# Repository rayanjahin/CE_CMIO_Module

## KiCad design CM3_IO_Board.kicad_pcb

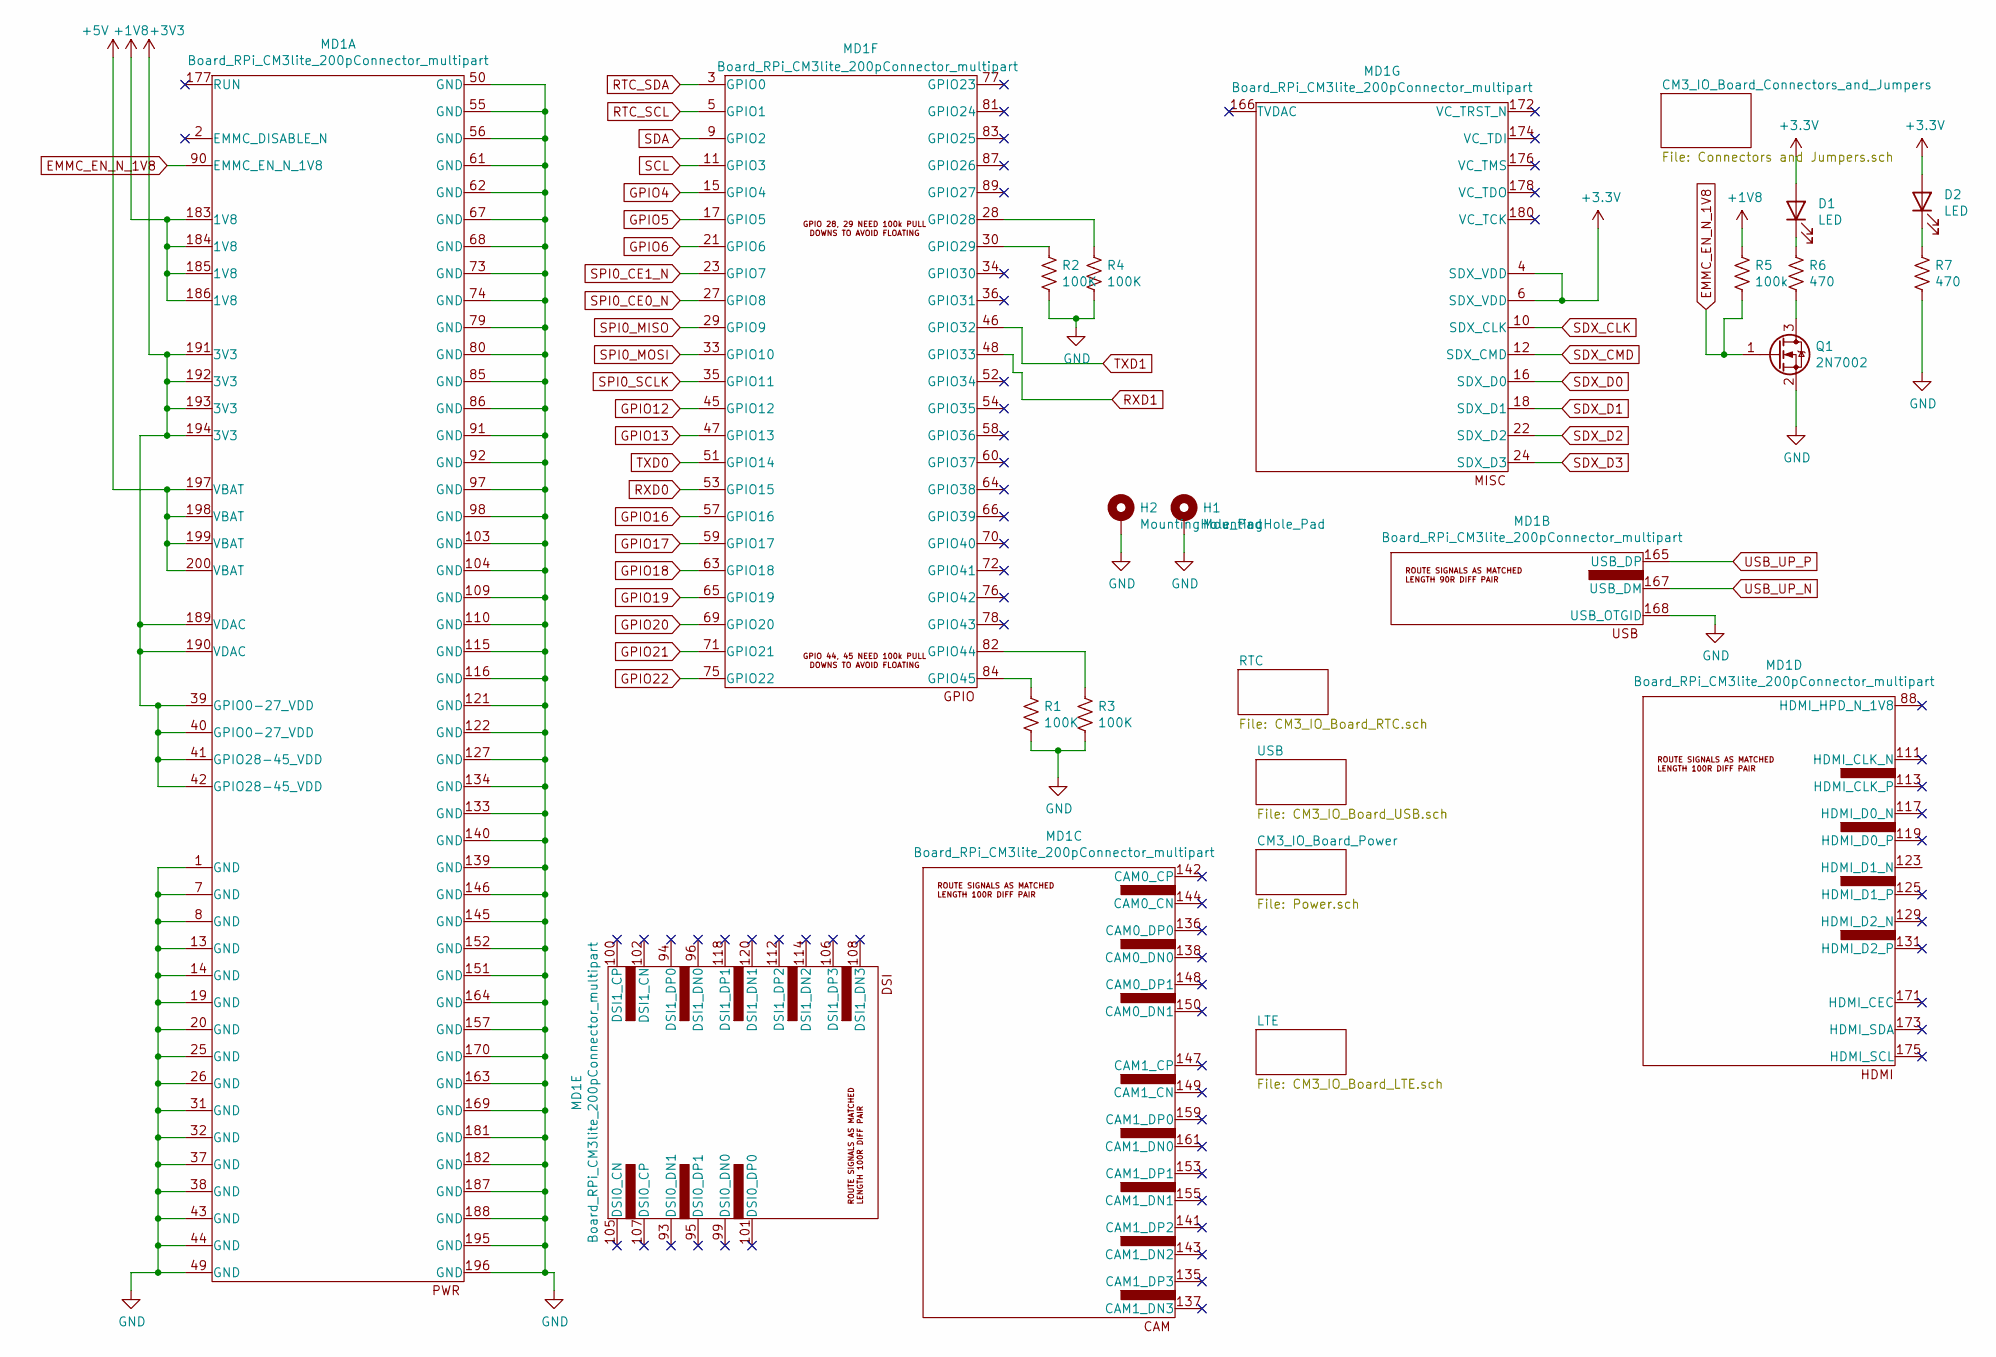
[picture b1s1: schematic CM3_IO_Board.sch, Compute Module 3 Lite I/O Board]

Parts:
D1, D2: LED; LED_1206_3216Metric
H1, H2: MountingHole_Pad; MountingHole_2.5mm_Pad_TopBottom
MD1: Board_RPi_CM3lite_200pConnector_multipart; Conn_TE-DDR2-SODIMM-0.6-200P-doublesided
Q1: 2N7002; SOT-23
R1, R2, R3, R4: 100K; R_1206_3216Metric
R5: 100k; R_1206_3216Metric
R6, R7: 470; R_1206_3216Metric

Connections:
+1V8: MD1.183 (1V8), MD1.184 (1V8), MD1.185 (1V8), MD1.186 (1V8), R5.1; also elsewhere on the board
+5V: MD1.197 (VBAT), MD1.198 (VBAT), MD1.199 (VBAT), MD1.200 (VBAT); also elsewhere on the board
EMMC_EN_N_1V8: MD1.90 (EMMC_EN_N_1V8), Q1.1 (G), R5.2
GND: H1.1, H2.1, MD1.1 (GND), MD1.7 (GND), MD1.8 (GND), MD1.13 (GND), MD1.14 (GND), MD1.19 (GND), MD1.20 (GND), MD1.25 (GND), MD1.26 (GND), MD1.31 (GND), MD1.32 (GND), MD1.37 (GND), MD1.38 (GND), MD1.43 (GND), MD1.44 (GND), MD1.49 (GND), MD1.50 (GND), MD1.55 (GND), MD1.56 (GND), MD1.61 (GND), MD1.62 (GND), MD1.67 (GND), MD1.68 (GND), MD1.73 (GND), MD1.74 (GND), MD1.79 (GND), MD1.80 (GND), MD1.85 (GND), MD1.86 (GND), MD1.91 (GND), MD1.92 (GND), MD1.97 (GND), MD1.98 (GND), MD1.103 (GND), MD1.104 (GND), MD1.109 (GND), MD1.110 (GND), MD1.115 (GND), MD1.116 (GND), MD1.121 (GND), MD1.122 (GND), MD1.127 (GND), MD1.133 (GND), MD1.134 (GND), MD1.139 (GND), MD1.140 (GND), MD1.145 (GND), MD1.146 (GND), MD1.151 (GND), MD1.152 (GND), MD1.157 (GND), MD1.163 (GND), MD1.164 (GND), MD1.168 (USB_OTGID), MD1.169 (GND), MD1.170 (GND), MD1.181 (GND), MD1.182 (GND), MD1.187 (GND), MD1.188 (GND), MD1.195 (GND), MD1.196 (GND), Q1.2 (S), R1.2, R2.2, R3.2, R4.2, R7.2; also elsewhere on the board
GPIO4: MD1.15 (GPIO4); also elsewhere on the board
GPIO5: MD1.17 (GPIO5); also elsewhere on the board
GPIO6: MD1.21 (GPIO6); also elsewhere on the board
GPIO12: MD1.45 (GPIO12); also elsewhere on the board
GPIO13: MD1.47 (GPIO13); also elsewhere on the board
GPIO16: MD1.57 (GPIO16); also elsewhere on the board
GPIO17: MD1.59 (GPIO17); also elsewhere on the board
GPIO18: MD1.63 (GPIO18); also elsewhere on the board
GPIO19: MD1.65 (GPIO19); also elsewhere on the board
GPIO20: MD1.69 (GPIO20); also elsewhere on the board
GPIO21: MD1.71 (GPIO21); also elsewhere on the board
GPIO22: MD1.75 (GPIO22); also elsewhere on the board
unnamed: D1.1 (K), R6.1
unnamed: D2.1 (K), R7.1
unnamed: MD1.28 (GPIO28), R4.1
unnamed: MD1.30 (GPIO29), R2.1
unnamed: MD1.82 (GPIO44), R3.1
unnamed: MD1.84 (GPIO45), R1.1
unnamed: Q1.3 (D), R6.2
RTC_SCL: MD1.5 (GPIO1); also elsewhere on the board
RTC_SDA: MD1.3 (GPIO0); also elsewhere on the board
RXD0: MD1.53 (GPIO15); also elsewhere on the board
RXD1: MD1.48 (GPIO33); also elsewhere on the board
SCL: MD1.11 (GPIO3); also elsewhere on the board
SDA: MD1.9 (GPIO2); also elsewhere on the board
SDX_CLK: MD1.10 (SDX_CLK); also elsewhere on the board
SDX_CMD: MD1.12 (SDX_CMD); also elsewhere on the board
SDX_D0: MD1.16 (SDX_D0); also elsewhere on the board
SDX_D1: MD1.18 (SDX_D1); also elsewhere on the board
SDX_D2: MD1.22 (SDX_D2); also elsewhere on the board
SDX_D3: MD1.24 (SDX_D3); also elsewhere on the board
SPI0_CE0_N: MD1.27 (GPIO8); also elsewhere on the board
SPI0_CE1_N: MD1.23 (GPIO7); also elsewhere on the board
SPI0_MISO: MD1.29 (GPIO9); also elsewhere on the board
SPI0_MOSI: MD1.33 (GPIO10); also elsewhere on the board
SPI0_SCLK: MD1.35 (GPIO11); also elsewhere on the board
TXD0: MD1.51 (GPIO14); also elsewhere on the board
TXD1: MD1.46 (GPIO32); also elsewhere on the board
USB_UP_N: MD1.167 (USB_DM); also elsewhere on the board
USB_UP_P: MD1.165 (USB_DP); also elsewhere on the board

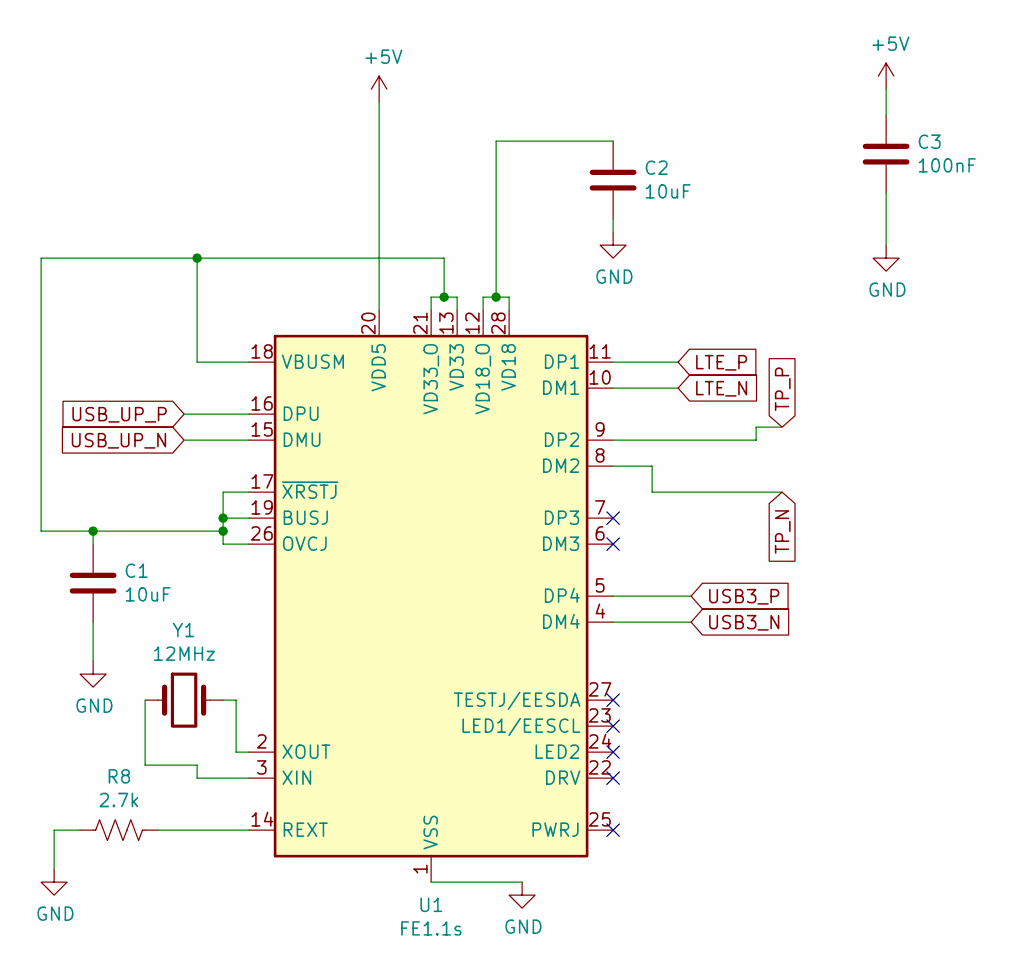
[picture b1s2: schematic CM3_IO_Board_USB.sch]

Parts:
C1, C2: 10uF; C_1206_3216Metric
C3: 100nF; C_0805_2012Metric
R8: 2.7k; R_1206_3216Metric
U1: FE1.1s; SSOP-28_3.9x9.9mm_P0.635mm
Y1: 12MHz; Crystal_HC18-U_Vertical

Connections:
+5V: C3.1, U1.20 (VDD5); also elsewhere on the board
GND: C1.2, C2.2, C3.2, R8.2, U1.1 (VSS); also elsewhere on the board
LTE_N: U1.10 (DM1); also elsewhere on the board
LTE_P: U1.11 (DP1); also elsewhere on the board
unnamed: C1.1, U1.13 (VD33), U1.17 (~XRSTJ), U1.18 (VBUSM), U1.19 (BUSJ), U1.21 (VD33_O), U1.26 (OVCJ)
unnamed: C2.1, U1.12 (VD18_O), U1.28 (VD18)
unnamed: R8.1, U1.14 (REXT)
unnamed: U1.2 (XOUT), Y1.2
unnamed: U1.3 (XIN), Y1.1
TP_N: U1.8 (DM2); also elsewhere on the board
TP_P: U1.9 (DP2); also elsewhere on the board
USB3_N: U1.4 (DM4); also elsewhere on the board
USB3_P: U1.5 (DP4); also elsewhere on the board
USB_UP_N: U1.15 (DMU); also elsewhere on the board
USB_UP_P: U1.16 (DPU); also elsewhere on the board

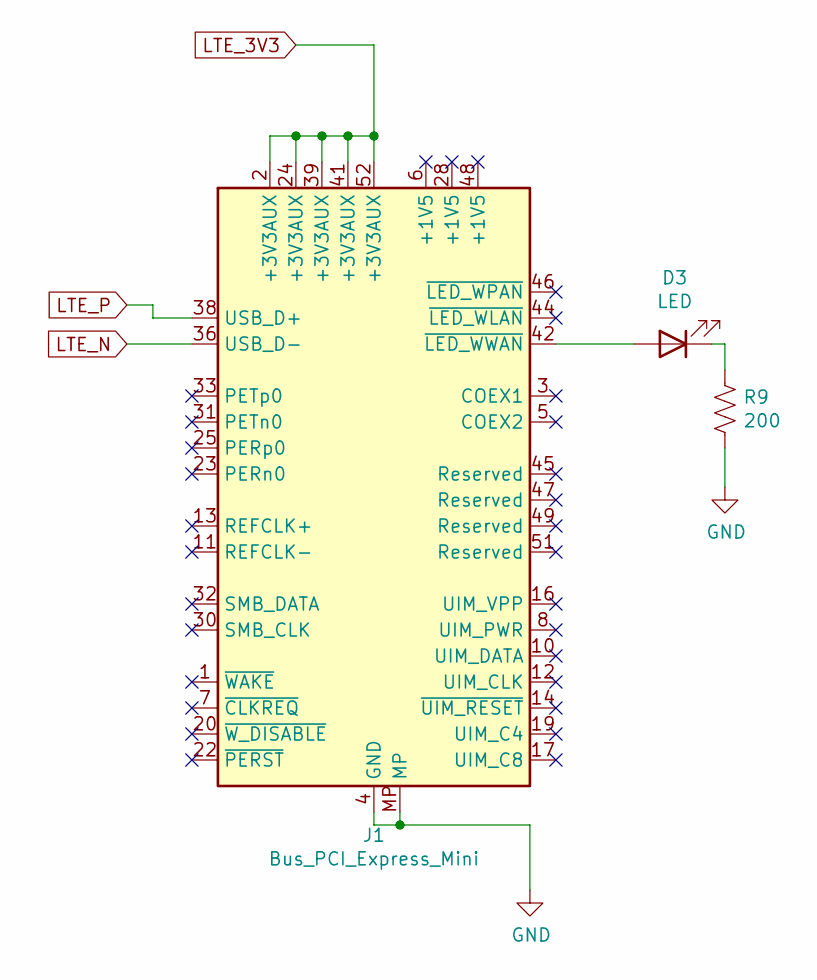
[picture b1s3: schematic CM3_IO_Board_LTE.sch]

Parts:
D3: LED; LED_1206_3216Metric
J1: Bus_PCI_Express_Mini; BUS_PCI_Express_Mini
R9: 200; R_1206_3216Metric

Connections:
GND: J1.4 (GND), J1.9 (GND), J1.15 (GND), J1.18 (GND), J1.21 (GND), J1.26 (GND), J1.27 (GND), J1.29 (GND), J1.34 (GND), J1.35 (GND), J1.37 (GND), J1.40 (GND), J1.43 (GND), J1.50 (GND), J1.MP, R9.2; also elsewhere on the board
LTE_3V3: J1.2 (+3V3AUX), J1.24 (+3V3AUX), J1.39 (+3V3AUX), J1.41 (+3V3AUX), J1.52 (+3V3AUX); also elsewhere on the board
LTE_N: J1.36 (USB_D-); also elsewhere on the board
LTE_P: J1.38 (USB_D+); also elsewhere on the board
unnamed: D3.1 (K), R9.1
unnamed: D3.2 (A), J1.42 (~LED_WWAN)

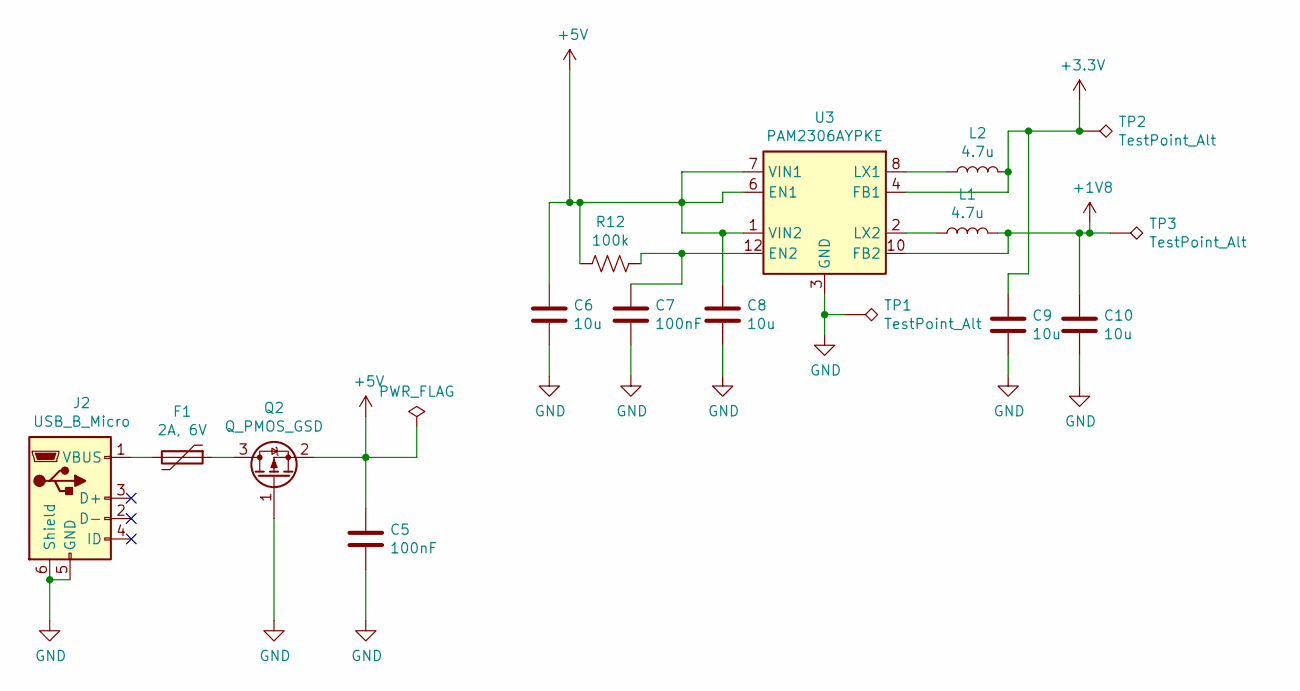
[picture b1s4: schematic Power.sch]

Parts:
C5, C7: 100nF; C_0805_2012Metric
C6, C8, C9, C10: 10u; C_1206_3216Metric
F1: 2A, 6V; Fuse_1812_4532Metric
J2: USB_B_Micro; USB_Micro-B_Amphenol_10118194_Horizontal
L1, L2: 4.7u; SRN4018
Q2: Q_PMOS_GSD; SOT-23
R12: 100k; R_1206_3216Metric
TP1, TP2, TP3: TestPoint_Alt; TestPoint_Pad_D2.0mm
U3: PAM2306AYPKE; WDFN-12-1EP_3x3mm_P0.45mm_EP1.7x2.5mm

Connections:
+1V8: C10.1, L1.2, TP3.1, U3.10 (FB2); also elsewhere on the board
+5V: C5.1, C6.1, C8.1, Q2.2 (S), R12.2, U3.1 (VIN2), U3.6 (EN1), U3.7 (VIN1); also elsewhere on the board
GND: C5.2, C6.2, C7.2, C8.2, C9.2, C10.2, J2.5 (GND), J2.6 (Shield), Q2.1 (G), TP1.1, U3.3 (GND), U3.9 (GND), U3.13 (GND); also elsewhere on the board
unnamed: C7.1, R12.1, U3.12 (EN2)
unnamed: F1.1, Q2.3 (D)
unnamed: F1.2, J2.1 (VBUS)
unnamed: L1.1, U3.2 (LX2)
unnamed: L2.1, U3.8 (LX1)

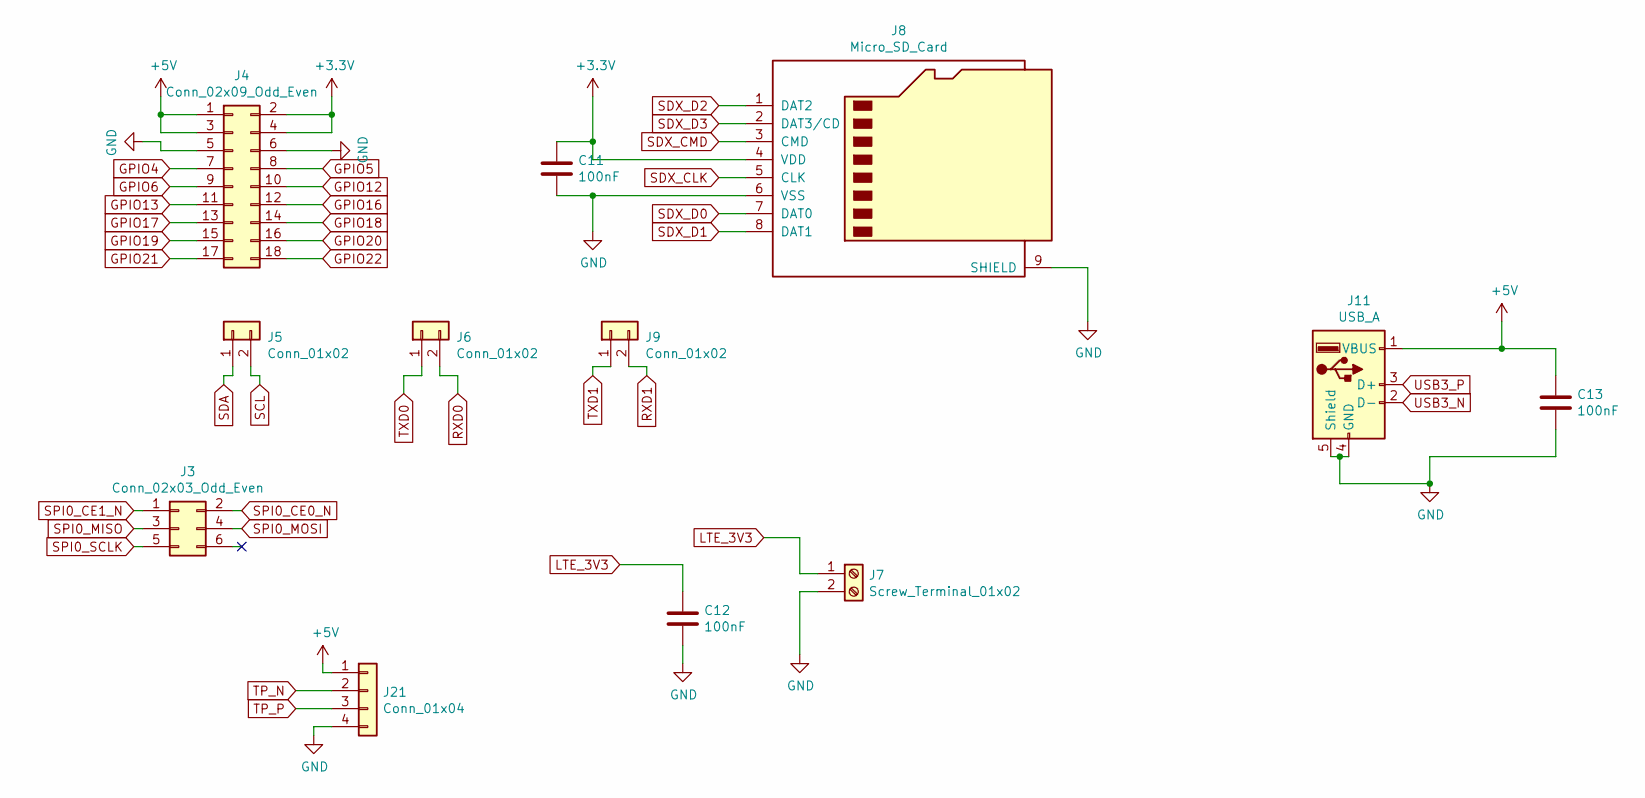
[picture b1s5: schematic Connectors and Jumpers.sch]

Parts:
C11, C12, C13: 100nF; C_0805_2012Metric
J3: Conn_02x03_Odd_Even; PinHeader_2x03_P2.54mm_Vertical
J4: Conn_02x09_Odd_Even; PinHeader_2x09_P2.54mm_Vertical
J5, J6, J9: Conn_01x02; PinHeader_1x02_P2.54mm_Vertical
J7: Screw_Terminal_01x02; Altech_AK300_1x02_P5.00mm_45-Degree
J8: Micro_SD_Card; microSD_HC_Hirose_DM3AT-SF-PEJM5
J11: USB_A; USB_A_Molex_67643_Horizontal
J21: Conn_01x04; PinSocket_1x04_P2.54mm_Vertical

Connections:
+5V: C13.1, J4.1, J4.3, J11.1 (VBUS), J21.1; also elsewhere on the board
GND: C11.2, C12.2, C13.2, J4.5, J4.6, J7.2, J8.6 (VSS), J8.9 (SHIELD), J11.4 (GND), J11.5 (Shield), J21.4; also elsewhere on the board
GPIO4: J4.7; also elsewhere on the board
GPIO5: J4.8; also elsewhere on the board
GPIO6: J4.9; also elsewhere on the board
GPIO12: J4.10; also elsewhere on the board
GPIO13: J4.11; also elsewhere on the board
GPIO16: J4.12; also elsewhere on the board
GPIO17: J4.13; also elsewhere on the board
GPIO18: J4.14; also elsewhere on the board
GPIO19: J4.15; also elsewhere on the board
GPIO20: J4.16; also elsewhere on the board
GPIO21: J4.17; also elsewhere on the board
GPIO22: J4.18; also elsewhere on the board
LTE_3V3: C12.1, J7.1; also elsewhere on the board
RXD0: J6.2; also elsewhere on the board
RXD1: J9.2; also elsewhere on the board
SCL: J5.2; also elsewhere on the board
SDA: J5.1; also elsewhere on the board
SDX_CLK: J8.5 (CLK); also elsewhere on the board
SDX_CMD: J8.3 (CMD); also elsewhere on the board
SDX_D0: J8.7 (DAT0); also elsewhere on the board
SDX_D1: J8.8 (DAT1); also elsewhere on the board
SDX_D2: J8.1 (DAT2); also elsewhere on the board
SDX_D3: J8.2 (DAT3/CD); also elsewhere on the board
SPI0_CE0_N: J3.2; also elsewhere on the board
SPI0_CE1_N: J3.1; also elsewhere on the board
SPI0_MISO: J3.3; also elsewhere on the board
SPI0_MOSI: J3.4; also elsewhere on the board
SPI0_SCLK: J3.5; also elsewhere on the board
TP_N: J21.2; also elsewhere on the board
TP_P: J21.3; also elsewhere on the board
TXD0: J6.1; also elsewhere on the board
TXD1: J9.1; also elsewhere on the board
USB3_N: J11.2 (D-); also elsewhere on the board
USB3_P: J11.3 (D+); also elsewhere on the board

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
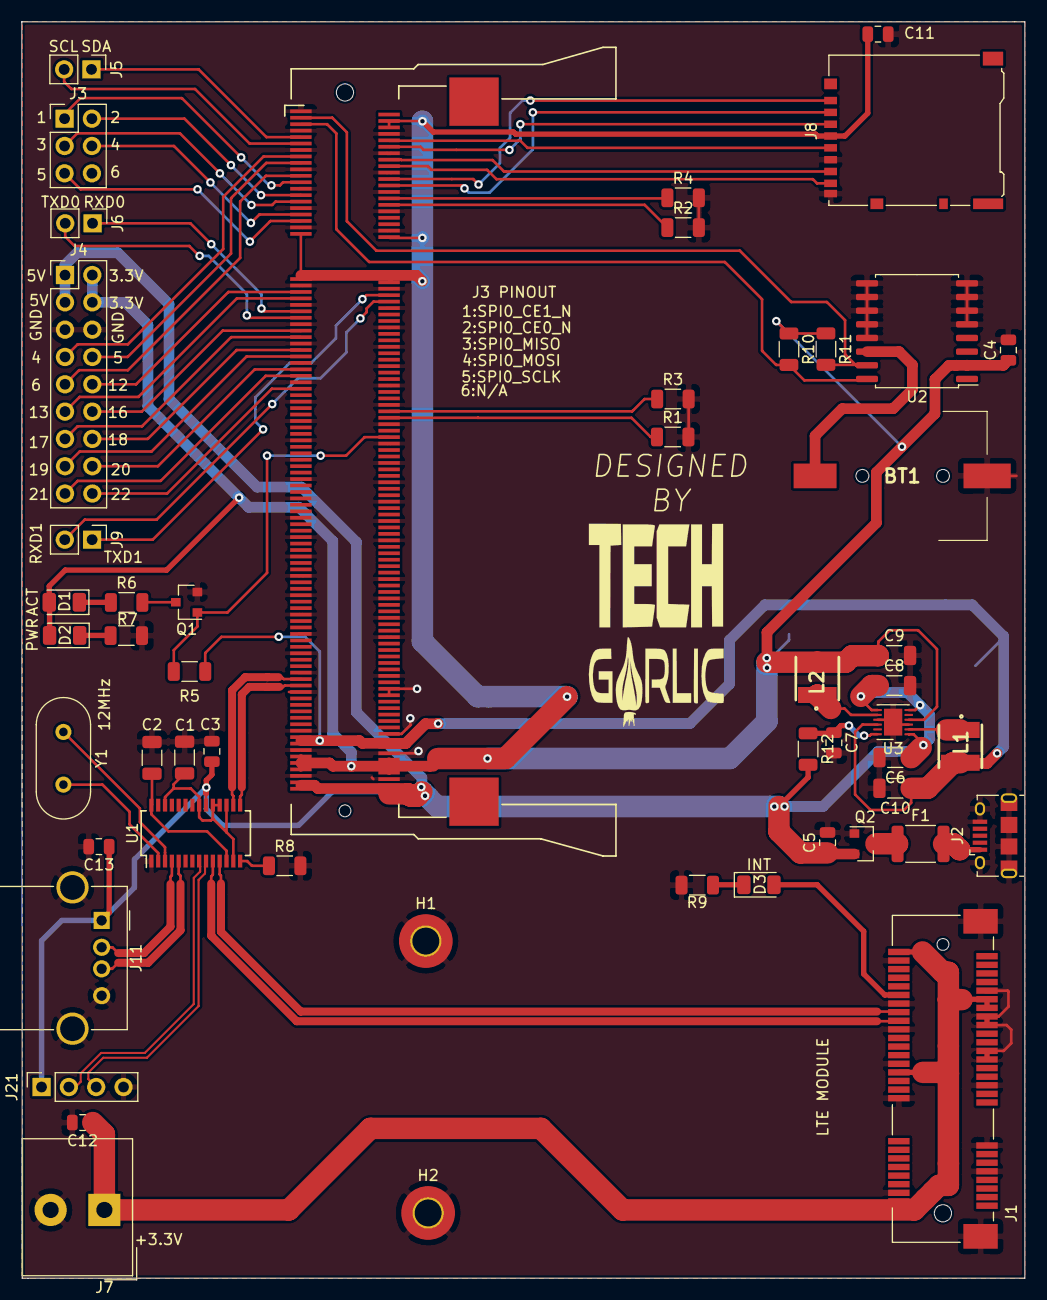
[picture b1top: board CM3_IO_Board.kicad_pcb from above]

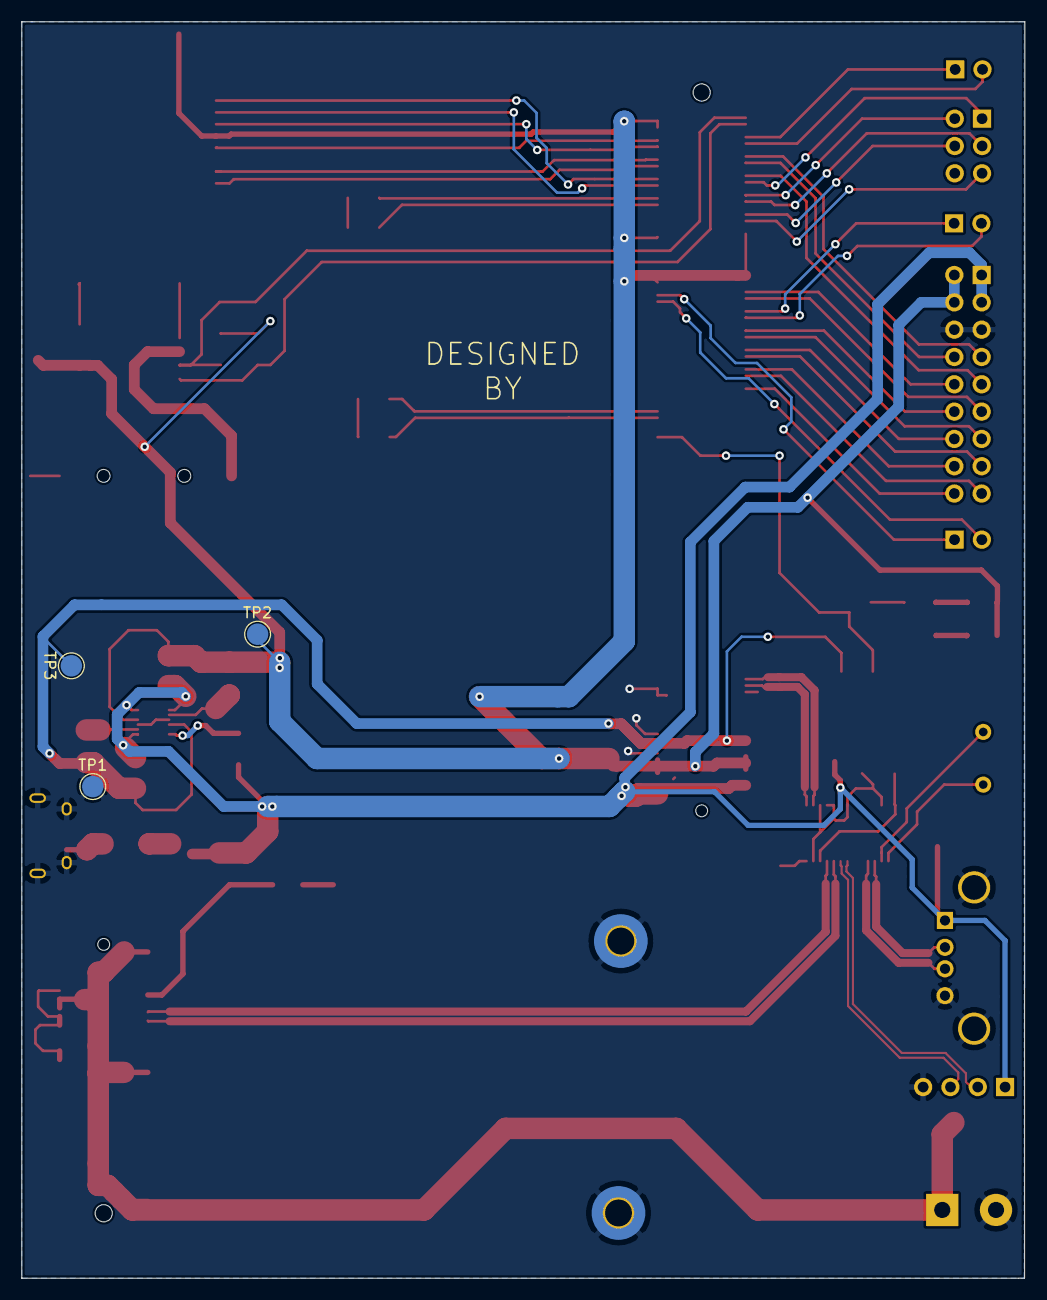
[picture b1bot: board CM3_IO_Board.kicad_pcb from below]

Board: 2 copper layers, 93.3 x 116.8 mm, 55 parts (3 on the bottom side), 65 nets.

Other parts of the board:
BT1: Battery_Cell; CR12202
C4: 100nF; C_0805_2012Metric
R10, R11: 10k; R_1206_3216Metric
U2: DS3231M; SOIC-16W_7.5x10.3mm_P1.27mm

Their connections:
GND: BT1.2, C4.2, U2.5, U2.6, U2.7, U2.8, U2.9, U2.10, U2.11, U2.12, U2.13; also elsewhere on the board
unnamed: BT1.1, U2.14
RTC_SCL: R10.2, U2.16; also elsewhere on the board
RTC_SDA: R11.2, U2.15; also elsewhere on the board

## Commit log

2022-06-29 added project to github
2022-06-30 5V connection point increased
2022-07-02 logo added
2022-07-03 gerber files and BOM and position file generated
2022-07-04 USB pinHeader added
